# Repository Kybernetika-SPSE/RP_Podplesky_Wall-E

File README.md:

# WALL-E Replika – Výroba a řízení modelu robota

Tento repozitář obsahuje kompletní podklady pro návrh, mechanickou stavbu, návrh elektroniky a vývoj řídicího softwaru funkční repliky robota **WALL-E**. Projekt vzniká na **VOŠ a SPŠE Plzeň** v rámci studijního oboru *Technické lyceum (78-42-M/01)*.

* **Autor:** Tomáš Podpleský
* **Vedoucí práce:** Ing. Pavel Jedlička
* **Škola:** VOŠ a SPŠE Plzeň, Koterovská 85

---

## 📋 Oficiální zadání prací

Vývoj projektu je rozdělen do dvou hlavních etap podle studijních ročníků:

* **3. ročník – Ročníková práce (2025/2026):**
  * 📄 [Zadání RP (PDF)](./3.%20Ročník/Zadani_RP_Podpleský.pdf) | [Textová verze](./3.%20Ročník/Zadani_RP_Podpleský.txt)
  * *Téma:* Model robota Wall-E
  * *Cíl:* Návrh a sestavení základního mechanického konceptu modelu se zaměřením na stabilitu, odpružení a pohyb pásového podvozku.

* **4. ročník – Dlouhodobá maturitní práce (2026/2027):**
  * 📄 [Zadání DMP (PDF)](./4.%20Ročník/zadání%20v1_final_final.pdf)
  * *Téma:* Výroba modelu robota Wall-E
  * *Cíl:* Návrh a konstrukce plně funkčního konceptu modelu s pásovým podvozkem, dálkově ovládaného pomocí bezdrátové myši s využitím analogových spínačů.
  * *Termín odevzdání:* 9. dubna 2027

---

## ⚙️ Technická specifikace a architektura

### 1. Šasi a mechanická konstrukce
* **Materiály:** Kombinace konstrukčních ocelových plátů (laserové pálení) a aditivní výroby (3D tisk dílů z technických termoplastů).
* **Podvozek:** Nezávisle odpružený pásový systém s mechanismem napínání pásů pro spolehlivý přenos točivého momentu v terénu.
* **3D data:** CAD modely a výkresová dokumentace v Autodesk Inventor / formátech STEP, DWG a STL.

### 2. Výpočetní jednotka
* **Hardware:** **NVIDIA Jetson Orin Nano**
* **Úloha:** Zpracování vstupních periferií v reálném čase, generování řídicích signálů pro budiče motorů, plánovaná telemetrie/odometrie a autonomní funkce.

### 3. Pohon a výkonová část
* **Motory:** 2× stejnosměrný převodový motor JGB37-550 (12 V).
* **Budiče (Drivery):** 2× H-můstek BTS7960B (špičkový proud až 43 A) pro obousměrné řízení a regulaci otáček pomocí PWM.
* **Chlazení:** Optimalizovaný vzduchový tunel (Wind Tunnel) s aktivním chlazením (40×40×10 mm ventilátor).

### 4. Vlastní elektronika a napájení
* **Distribuce napájení (Power Hub):** Zakázková deska plošných spojů vyvíjená v prostředí **KiCad** ([`4. Ročník/ELEKTRO/PCB/`](./4.%20Ročník/ELEKTRO/PCB/)).
* **Měniče napětí:** Step-Down moduly LM2596 / HW-411 pro stabilní napájení Jetsonu a logiky.
* **Akumulátory:** Duální bateriový subsystém (Li-Po 3S).

### 5. Řídicí software a ovládání
* **Primární ovládání:** Bezdrátová myš Logitech s protokolem **Logitech HID++ 2.0**. Z USB/HID reportů se čte přítlak analogových tlačítek.
* **Záložní ovládání:** Pokud při spuštění není dostupný HID dongle myši, program hledá připojený DualSense. Ovladač musí být s Jetsonem předem spárovaný a připojený přes Bluetooth.
  * Levý thumbstick ovládá levý pás, pravý thumbstick pravý pás; pohyb nahoru jede dopředu a dolů dozadu.
  * Změny rychlosti z thumbsticků se omezují plynulým rozjezdem a brzděním.
  * L2 otáčí doleva, R2 doprava; rychlost otáčení odpovídá míře stisknutí triggeru.
  * Šipka nahoru/dolů na směrovém kříži při držení rozjíždí robota rovně dopředu/dozadu; po puštění rychlost plynule klesá k nule.
  * Současné stisknutí Create a Options zastaví motory; stejná kombinace ovládání znovu aktivuje.
  * Při odpojení aktivního ovladače se vstupy vynulují a motory okamžitě zastaví.
* **Implementace:** Řídicí jádro v C++ ([`cpp_core/`](./4.%20Ročník/cpp_core/)) automaticky detekuje vstupy přes Linux `evdev`; myš má před DualSense přednost. Pythonové skripty ([`analog_mouse.py`](./4.%20Ročník/analog_mouse.py), [`test_mouse.py`](./4.%20Ročník/test_mouse.py)) slouží k prototypování a diagnostice myši.

---

## 📂 Struktura repozitáře

```text
Wall-E/
├── README.md                          # Hlavní přehled projektu a dokumentace
├── .gitignore                         # Konfigurace ignorovaných souborů pro Git
│
├── 3. Ročník/                         # Etapa 3. ročníku (Základní koncept a mechanika)
│   ├── Zadani_RP_Podpleský.pdf        # Oficiální zadání ročníkové práce
│   ├── Zadani_RP_Podpleský.txt        # Textová verze zadání RP
│   ├── code/                          # Původní zdrojové kódy (C, C++, Python)
│   ├── Elektronika/                   # Původní schémata zapojení (Příloha I)
│   ├── MODEL/                         # 3D sestavy a modely (Inventor)
│   ├── STEP/                          # Exporty sestav ve formátu STEP
│   ├── STL/                           # Podklady pro 3D tisk
│   ├── VÝKRESY/                       # Výrobní výkresy (DWG, PDF) pro laser cut
│   ├── FOTKY/                         # Foto a render dokumentace podvozku a pásů
│   └── prezentace/                    # Prezentace k obhajobě ročníkové práce
│
└── 4. Ročník/                         # Etapa 4. ročníku (DMP – Finální elektronika a řízení)
    ├── zadání v1_final_final.pdf      # Oficiální zadání dlouhodobé maturitní práce
    ├── ELEKTRO/                       # KiCad projekt zakázkové desky (Wall-E Power Hub)
    │   └── PCB/                       # Schémata, DPS a 3D STEP modely desky
    ├── cpp_core/                      # C++ řídicí jádro (CMake, evdev rozhraní)
    ├── Modely/                        # Doplňující 3D STEP/STL modely komponent (drivery, měniče)
    ├── analog_mouse.py                # Skript pro čtení analogových dat tlačítek z HID++
    ├── test_mouse.py                  # Testovací utilita pro ověření vstupů myši
    ├── Wall-E_Harmonogram.ics         # Kalendářní harmonogram vývoje a konzultací
    ├── Zdroje.txt                     # Rešerše odborných zdrojů, knihoven a podkladů
    └── napady.txt                     # Backlog plánovaných funkcí (odometrie, telemetrie)
```

---

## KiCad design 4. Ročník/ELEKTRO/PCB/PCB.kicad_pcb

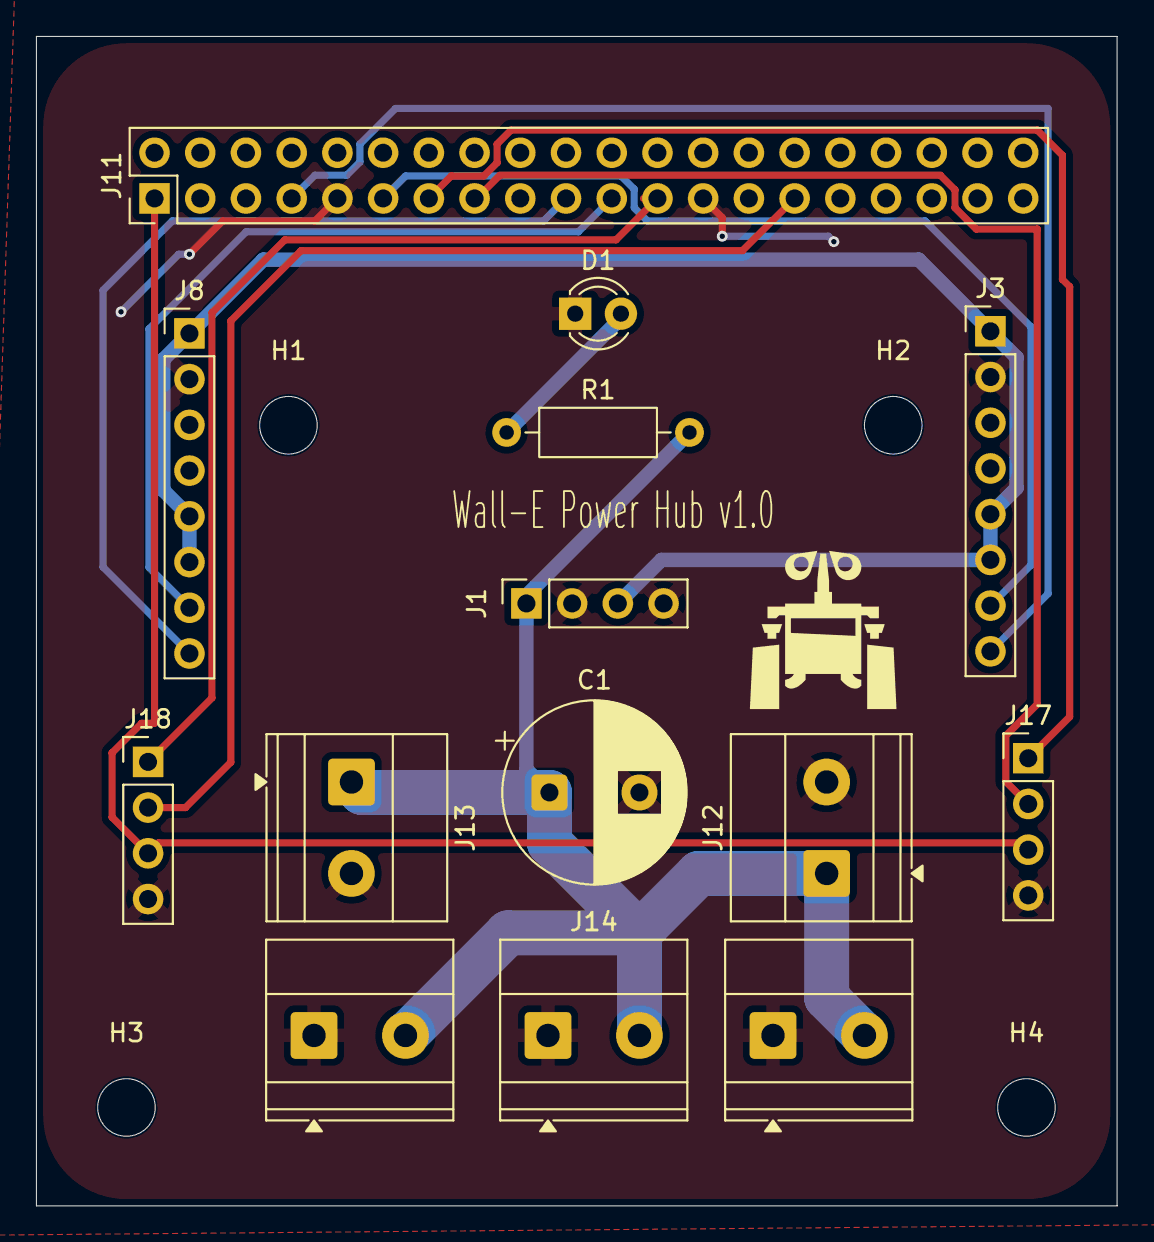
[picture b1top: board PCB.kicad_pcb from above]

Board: 2 copper layers, 60.0 x 65.0 mm, 18 parts (0 on the bottom side), 13 nets.

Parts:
C1: 1000uF / 35V; CP_Radial_D10.0mm_P5.00mm
D1: LED; LED_D3.0mm
H1, H2, H3, H4: MountingHole; MountingHole_3.2mm_M3
J1: Conn_01x04; PinSocket_1x04_P2.54mm_Vertical
J3, J8: Conn_01x08; PinHeader_1x08_P2.54mm_Vertical
J11: Jetson Pinout; PinHeader_2x20_P2.54mm_Vertical
J12, J13, J14: Screw_Terminal_01x02; TerminalBlock_Phoenix_MKDS-1,5-2-5.08_1x02_P5.08mm_Horizont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
J15: Napajeni BTS_R; TerminalBlock_Phoenix_MKDS-1,5-2-5.08_1x02_P5.08mm_Horizont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
J16: Napajeni BTS_L; TerminalBlock_Phoenix_MKDS-1,5-2-5.08_1x02_P5.08mm_Horizont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
J17, J18: Conn_01x04; PinHeader_1x04_P2.54mm_Vertical
R1: 1k; R_Axial_DIN0207_L6.3mm_D2.5mm_P10.16mm_Horizontal

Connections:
+3V3: J11.1, J17.3, J18.3
+5V: J1.3, J3.1, J3.5, J3.6, J8.1, J8.5, J8.6
+12V: C1.1, J1.1, J12.1, J13.1, J14.2, J15.2, J16.2, R1.2
/L_LPWM: J8.8, J11.19
/L_RPWM: J8.7, J11.21
/MOTOR_L_ENK_A: J11.23, J18.1
/MOTOR_L_ENK_B: J11.29, J18.2
/MOTOR_R_ENK_A: J11.13, J17.1
/MOTOR_R_ENK_B: J11.15, J17.2
/R_LPWM: J3.8, J11.7
/R_RPWM: J3.7, J11.11
GND: C1.2, D1.1 (K), J1.2, J1.4, J3.2, J8.2, J11.9, J11.25, J12.2, J13.2, J14.1, J15.1, J16.1, J17.4, J18.4
unnamed: D1.2 (A), R1.1

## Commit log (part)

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2025-11-13 Creating files, DWG and research
2025-11-25 Add camera link to random komponenty
2025-12-10 Frame.stl created
2025-12-15 Add header to random komponenty.md
2025-12-15 Format links as markdown in random komponenty.md
2025-12-15 Remove duplicate links in random komponenty.md
2026-02-16 Revise components list for wall-E project
    Updated the components list for wall-E with detailed specifications and requirements.
2026-02-16 Remove comments from components list
    Removed comments about motor robustness and driver logic level requirements.
2026-02-16 Refine component specifications in komponenty.md
    Updated component list with specific model names and removed some items.
2026-02-17 Update všech souborů
2026-02-18 Pridani dokumentace a zacatek kodu
2026-02-18 Aktualizace README
2026-02-18 Reorganizace slozek a .gitignore
2026-02-18 Aktualizace nakupniho seznamu a schema zapojeni
2026-02-18 Oprava diagramu a finalizace dokumentace
2026-02-19 přidání ceny
2026-02-19 oprava formátu
2026-02-19 úprava readme
2026-04-01 Update .gitignore: Ignore .agents, workspace, AUTOCAD, Blueprint
2026-04-03 Obnova dwg souborů a modelů - přesunuto do VÝKRESY
2026-04-03 Obnova výkresu spodního kusu z cache (OldVersions)
2026-04-14 Aktualizace CAD modelů, přidání STEP, STL a výkresů
2026-04-15 Revize a kompletace CAD výkresů pro Wall-E (Materiály, tolerance, STEP modely, PDF)
2026-04-23 feat(firmware): Initialize ESP32-S3 PlatformIO project and backup old C code
2026-06-16 Add documentation for encoders and MicroPython example
    Added detailed explanation of encoders, including types, working principles, and example code in MicroPython for reading rotary encoders using interrupts.
2026-06-16 Enhance nevim.md with encoder examples and formatting
    Updated text formatting and added code examples for encoder handling in MicroPython.
2026-06-16 Fix iframe source URL in nevim.md
2026-06-16 Modify iframe for interactive simulation
    Updated iframe source URL to include embed parameter.
